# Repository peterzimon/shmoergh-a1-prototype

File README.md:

# Shmøergh A1 — Semi-modular analog monosynth

A1 is a fully analog semi-modular monosynth. I took the Minimoog as my main inspiration for its sound but of course the circuitry is nowhere comparable with it. The synth has a default hardwired patch inside, it has a couple of modulation sources and targets so we can consider it semi-modular. Everything is handmade by me at home. Most of the module circuits are based on very well-known schematics and a few of the circuits are original. 

### Features
- Fat AF analog sound, fun
- Two voices with 3 waveshapes (saw, triangle, pulse) and additional noise and square suboscillator sound sources
- 24dB/oct diode low pass filter with self-resonance and dedicated envelope generator
- Triangle and square waveform LFO
- Mod matrix for overriding default patch
- Follows Eurorack standards: 10Vpp signal and modulation, 0-8V envelope levels
- All modules are designed and built on separate PCBs for reusability and experimenting

### What's in this repo?
You can find all the **KiCad 5** files (schematics and PCB design) of the synth here.

---

### License and disclaimer
All circuits, schematics, printed circuit board, panel design and associated data published within this project can be used for private use only. The author, host, and all people associated with these circuits disclaim any liability for damages should anyone be killed or injured while working on these projects, or projects based on these designs, or any other project or design presented in these schematics. The author, host, and all people associated with these circuits also disclaim any liability for projects, or projects based on these designs, or any other project or design presented on these web pages and any associated web pages when used in such a way as to infringe relevant government regulations and by-laws.

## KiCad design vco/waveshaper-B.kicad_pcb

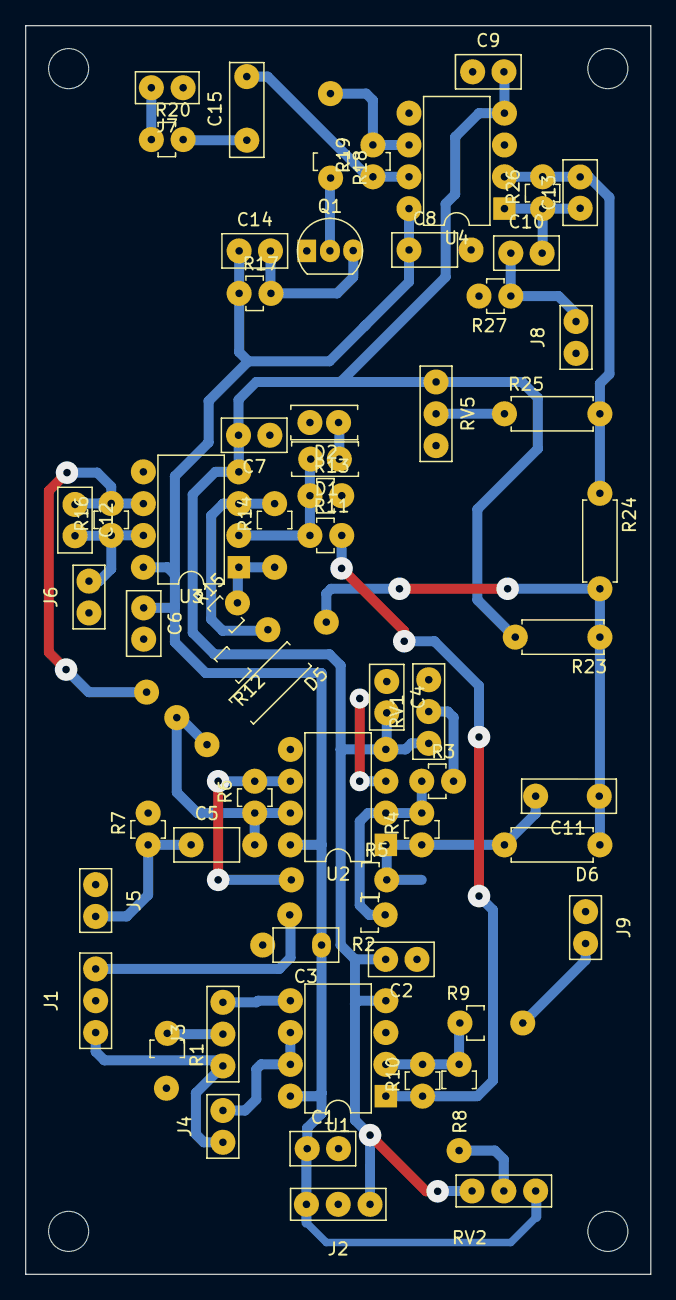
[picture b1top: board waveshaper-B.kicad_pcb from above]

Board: 2 copper layers, 49.9 x 99.7 mm, 61 parts (0 on the bottom side), 35 nets.

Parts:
C1, C2, C3, C4, C6, C7, C8, C9, C14: 100n; C_Disc_D5.0mm_W2.5mm_P2.50mm
C5, C10: 470n; C_Disc_D5.0mm_W2.5mm_P2.50mm
C11: 2.2n foil; C_Foil_P5.48mm
C12, C13: 22p; C_Disc_D5.0mm_W2.5mm_P2.50mm
C15: 1u; C_Foil_P5.48mm
D1, D2: 4.7V; D_Axial-Vertical
D5, D6: 1N4148; D_Axial
J1: In + 5VPower; NSL25_01x03_Vertical
J2: Power; NSL25_01x03_Vertical
J3: Course Switch IO; NSL25_01x03_Vertical
J4: Coarse VCO IO; NSL25_01x02_Vertical
J5: Saw Out; NSL25_01x02_Vertical
J6: Square Out; NSL25_01x02_Vertical
J7: Noise Out; NSL25_01x02_Vertical
J8: Tri Out; NSL25_01x02_Vertical
J9: PWM; NSL25_01x02_Vertical
Q1: BC548; TO-92_Inline
R1: 1.5k (0.1%); R_Axial_Vertical
R2: 10k; R_Axial_Vertical
R3, R12, R18: 2.2k; R_Axial_Vertical
R4: 15k; R_Axial_Vertical
R5, R6, R10, R16: 100k; R_Axial_Vertical
R7, R27: 1M; R_Axial_Vertical
R8: 150k; R_Axial_Vertical
R9, R11: 47k; R_Axial_Vertical
R13, R26: 220k; R_Axial_Vertical
R14: 2.2M; R_Axial_Vertical
R15: 240k; R_Axial_Vertical
R17: 470k; R_Axial_Vertical
R19: 3.3M; R_Axial_Vertical
R20: 1k; R_Axial_Vertical
R23: 10k; R_Axial_DIN0207_L6.3mm_D2.5mm_P7.62mm_Horizontal
R24, R25: 100k; R_Axial_DIN0207_L6.3mm_D2.5mm_P7.62mm_Horizontal
RV1: 10k; PinOut_01x03
RV2: 100k; NSL25_01x03_Vertical
RV5: 100k; PinOut_01x03
U1, U2, U3, U4: TL072; DIP-8_W7.62mm

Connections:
+12V: C1.1, C3.1, C6.1, C8.1, C14.1, J2.1, R17.1, RV2.1, U1.8, U2.8, U3.8, U4.8
-5V: J1.3, J3.3, J4.2
-12V: C2.2, C4.2, C7.2, C9.2, J2.3, R23.2, RV1.3, RV2.3, RV5.3, U1.4, U2.4, U3.4, U4.4
COARSE: J3.1, U1.5
CV_PWM: J9.1, R9.2
GND: C1.2, C2.1, C3.2, C4.1, C6.2, C7.1, C8.2, C9.1, D2.2, J2.2, J5.2, J6.2, J7.2, J8.2, J9.2, R1.2, R7.2, R13.2, R27.2, RV1.1, RV5.1, U1.3, U2.3, U2.5, U3.5, U4.3, U4.5
unnamed: C10.2, C13.1, R26.1, U4.1
unnamed: C11.1, D5.1, D6.1, R23.1, R24.2
unnamed: C12.1, R15.1, R16.2, U3.6
unnamed: C13.2, R24.1, R25.2, R26.2, U4.2
unnamed: C14.2, Q1.3, R17.2
unnamed: C15.1, R20.2
unnamed: C15.2, R19.1, U4.7
unnamed: D1.1, D2.1
unnamed: D1.2, R11.1, R13.1, U3.2
unnamed: J3.2, R1.1
unnamed: J4.1, U1.6, U1.7
unnamed: Q1.2, R18.2
unnamed: R2.1, R3.1, R4.2, U2.2
unnamed: R3.2, RV1.2
unnamed: R5.1, R6.2, U2.6
unnamed: R8.2, RV2.2
unnamed: R8.1, R9.1, R10.2, U1.2
unnamed: R12.1, R14.2, U3.3
unnamed: R14.1, R15.2, U3.1
unnamed: R18.1, R19.2, U4.6
unnamed: R25.1, RV5.2
OUT_NOISE: J7.1, R20.1
OUT_SAW: C5.1, J5.1, R7.1
OUT_SQR: C12.2, J6.1, R16.1, U3.7
OUT_TRI: C10.1, J8.1, R27.1
PWM: R10.1, R11.2, U1.1
RAW_SAW: J1.1, R2.2
SAW_DBL_INV: C5.2, D5.2, R6.1, R12.2, U2.7
SAW_INV: C11.2, D6.2, R4.1, R5.2, U2.1

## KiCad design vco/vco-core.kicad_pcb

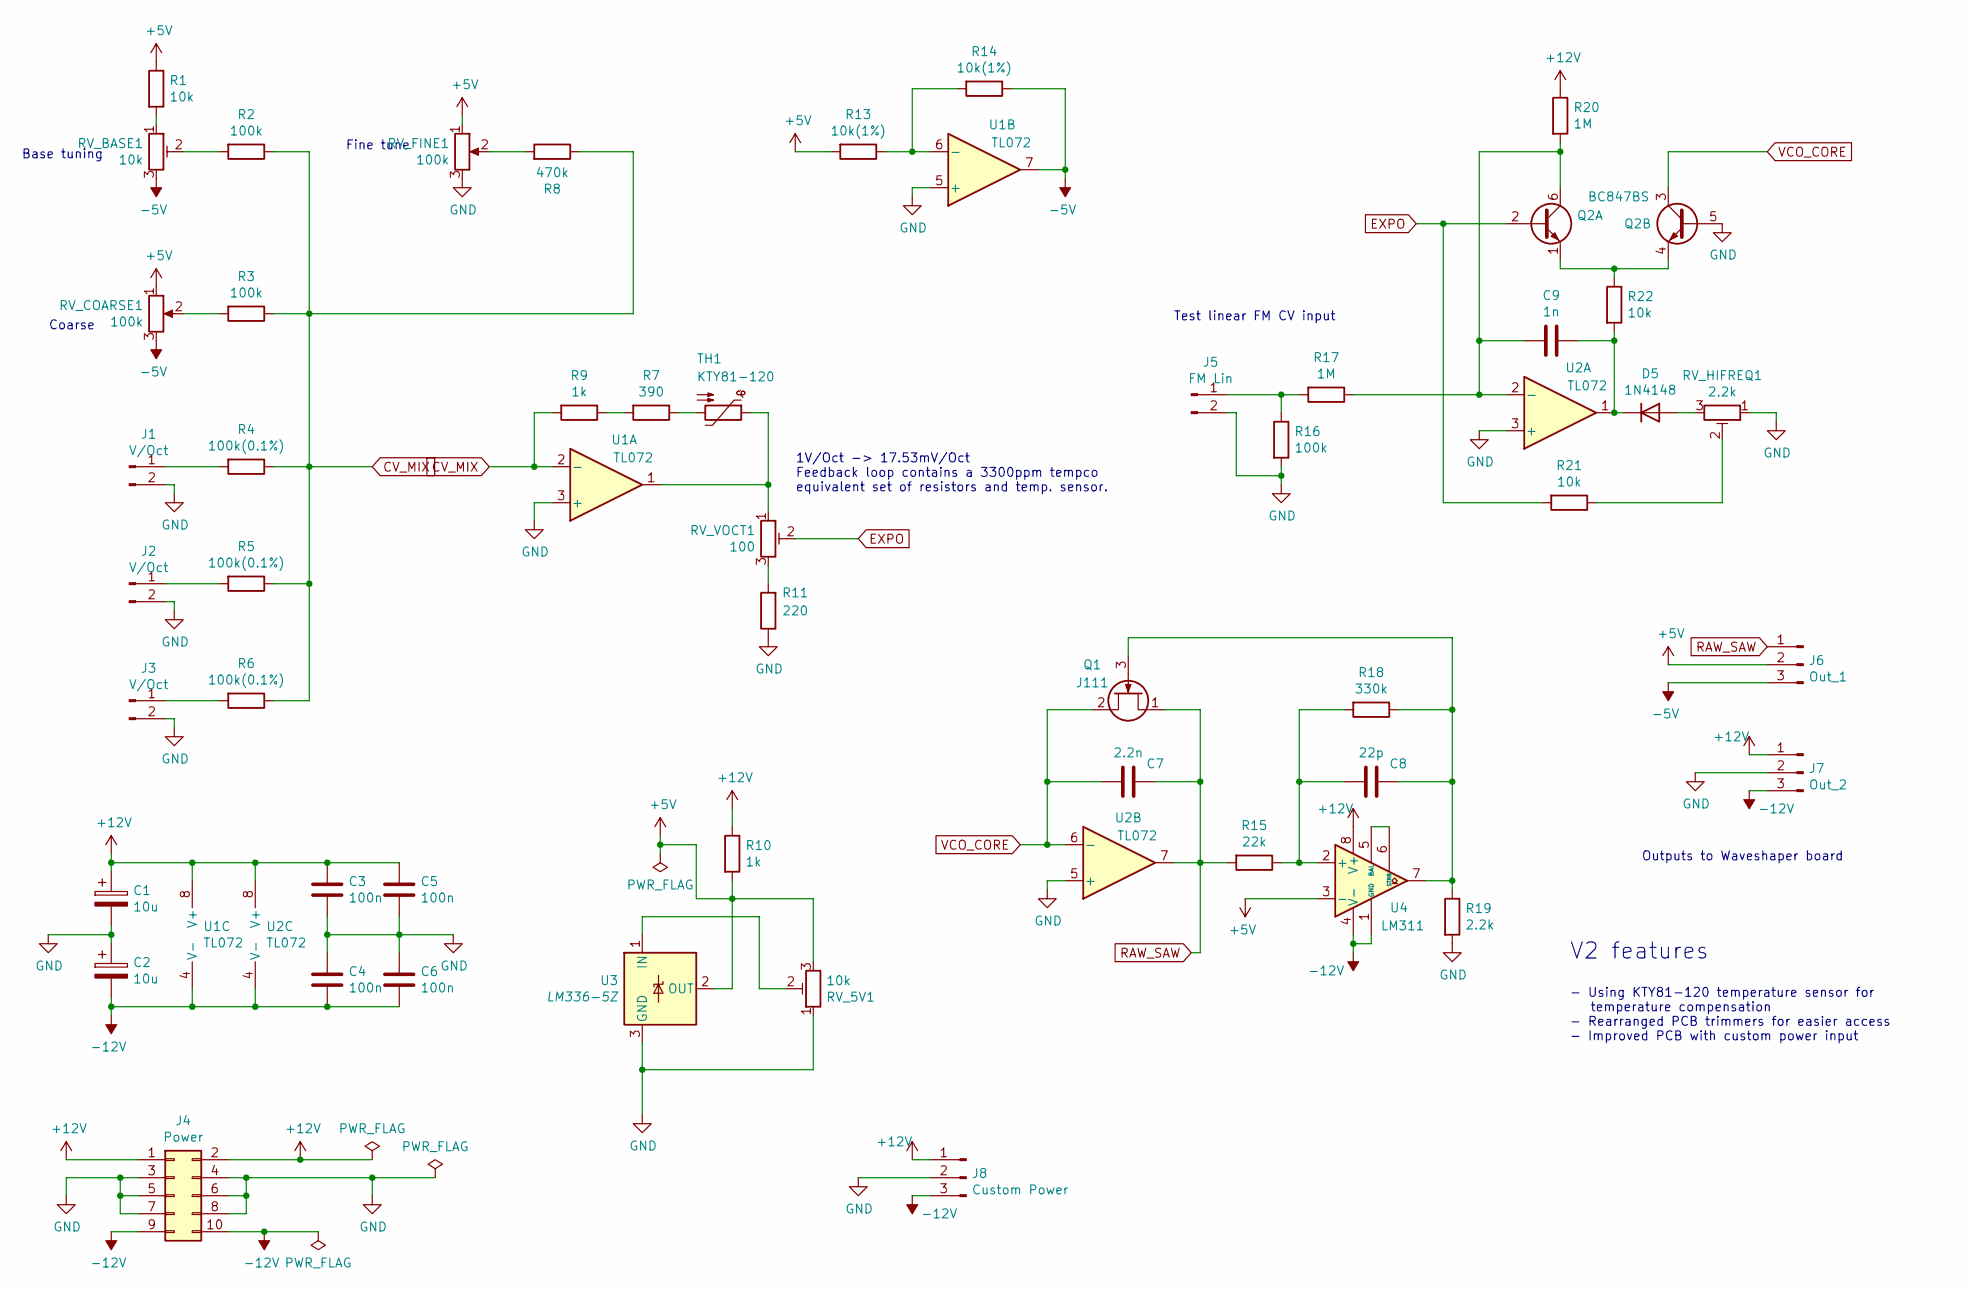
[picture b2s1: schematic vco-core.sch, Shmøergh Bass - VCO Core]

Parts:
C1, C2: 10u; CP_Radial_D5.0mm_P2.50mm
C3, C4, C5, C6: 100n; C_Disc_D5.0mm_W2.5mm_P2.50mm
C7: 2.2n; C_Disc_D5.0mm_W2.5mm_P2.50mm
C8: 22p; C_Disc_D5.0mm_W2.5mm_P2.50mm
C9: 1n; C_Disc_D5.0mm_W2.5mm_P2.50mm
D5: 1N4148; D_Axial-Vertical
J1, J2, J3: V/Oct; NSL25_01x02_Vertical
J4: Power; Eurorack_Power_Supply
J5: FM Lin; NSL25_01x02_Vertical
J6: Out_1; NSL25_01x03_Vertical
J7: Out_2; NSL25_01x03_Vertical
J8: Custom Power; NSL25_01x03_Vertical
Q1: J111; TO-92_Inline
Q2: BC847BS; SOT-363_SC-70-6
R1, R21, R22: 10k; R_Axial_Vertical
R2, R3, R16: 100k; R_Axial_Vertical
R4, R5, R6: 100k(0.1%); R_Axial_Vertical
R7: 390; R_Axial_Vertical
R8: 470k; R_Axial_Vertical
R9, R10: 1k; R_Axial_Vertical
R11: 220; R_Axial_Vertical
R13, R14: 10k(1%); R_Axial_Vertical
R15: 22k; R_Axial_Vertical
R17, R20: 1M; R_Axial_Vertical
R18: 330k; R_Axial_Vertical
R19: 2.2k; R_Axial_Vertical
RV_5V1: 10k; PinOut_01x03
RV_BASE1: 10k; PinOut_01x03
RV_COARSE1: 100k; NSL25_01x03_Vertical
RV_FINE1: 100k; NSL25_01x03_Vertical
RV_HIFREQ1: 2.2k; PinOut_01x03
RV_VOCT1: 100; PinOut_01x03
TH1: KTY81-120; R_Axial_DIN0207_L6.3mm_D2.5mm_P7.62mm_Horizontal
U1, U2: TL072; DIP-8_W7.62mm
U3: LM336-5Z; TO-92_Inline
U4: LM311; DIP-8_W7.62mm

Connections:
+5V: J6.2, R1.1, R10.2, R13.2, RV_5V1.3, RV_COARSE1.1, RV_FINE1.1, U3.2 (OUT), U4.3 (-)
+12V: C1.1, C3.1, C5.1, J4.1, J4.2, J7.1, J8.1, R10.1, R20.1, U1.8 (V+), U2.8 (V+), U4.8 (V+)
-5V: J6.3, R14.1, RV_BASE1.3, RV_COARSE1.3, U1.7
-12V: C2.2, C4.2, C6.2, J4.9, J4.10, J7.3, J8.3, U1.4 (V-), U2.4 (V-), U4.1 (GND), U4.4 (V-)
CV_MIX: R2.1, R3.1, R4.1, R5.1, R6.1, R8.1, R9.2, U1.2 (-)
EXPO: Q2.2 (B1), R21.2, RV_VOCT1.2
GND: C1.2, C2.1, C3.2, C4.1, C5.2, C6.1, J1.2, J2.2, J3.2, J4.3, J4.4, J4.5, J4.6, J4.7, J4.8, J5.2, J7.2, J8.2, Q2.5 (B2), R11.1, R16.2, R19.2, RV_5V1.1, RV_FINE1.3, RV_HIFREQ1.1, U1.3 (+), U1.5 (+), U2.3 (+), U2.5 (+), U3.3 (GND)
unnamed: C8.1, Q1.3 (G), R18.1, R19.1, U4.7
unnamed: C8.2, R15.1, R18.2, U4.2 (+)
unnamed: C9.1, D5.1 (K), R22.2, U2.1
unnamed: C9.2, Q2.6 (C1), R17.1, R20.2, U2.2 (-)
unnamed: D5.2 (A), RV_HIFREQ1.3
unnamed: J1.1, R4.2
unnamed: J2.1, R5.2
unnamed: J3.1, R6.2
unnamed: J5.1, R16.1, R17.2
unnamed: Q2.1 (E1), Q2.4 (E2), R22.1
unnamed: R1.2, RV_BASE1.1
unnamed: R2.2, RV_BASE1.2
unnamed: R3.2, RV_COARSE1.2
unnamed: R7.1, TH1.2
unnamed: R7.2, R9.1
unnamed: R8.2, RV_FINE1.2
unnamed: R11.2, RV_VOCT1.3
unnamed: R13.1, R14.2, U1.6 (-)
unnamed: R21.1, RV_HIFREQ1.2
unnamed: RV_5V1.2, U3.1 (IN)
unnamed: RV_VOCT1.1, TH1.1, U1.1
unnamed: U4.5 (BAL), U4.6 (STRB)
RAW_SAW: C7.1, J6.1, Q1.1 (D), R15.2, U2.7
VCO_CORE: C7.2, Q1.2 (S), Q2.3 (C2), U2.6 (-)

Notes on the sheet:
Coarse
Base tuning
Fine tune
Outputs to Waveshaper board
Test linear FM CV input
V2 features
- Using KTY81-120 temperature sensor for temperature compensation - Rearranged PCB trimmers for easier access - Improved PCB with custom power input
1V/Oct -> 17.53mV/Oct Feedback loop contains a 3300ppm tempco equivalent set of resistors and temp. sensor.

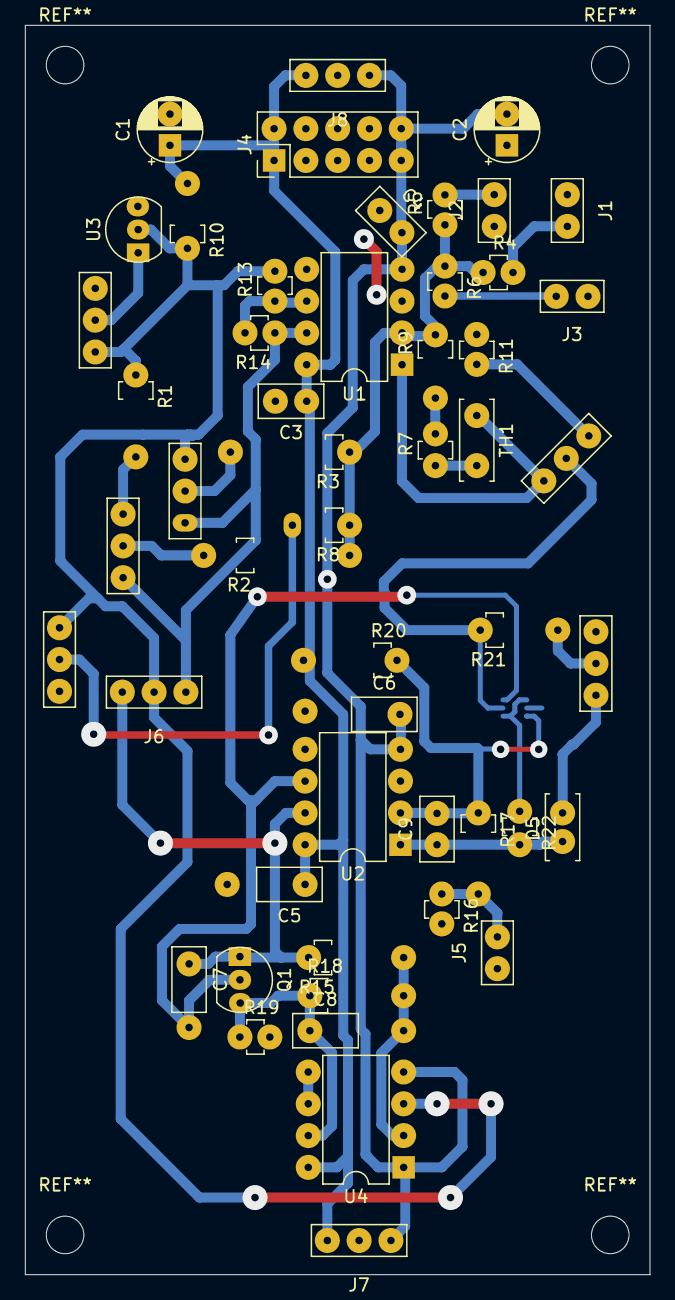
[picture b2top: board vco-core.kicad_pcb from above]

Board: 2 copper layers, 49.9 x 99.8 mm, 52 parts (1 on the bottom side), 31 nets.

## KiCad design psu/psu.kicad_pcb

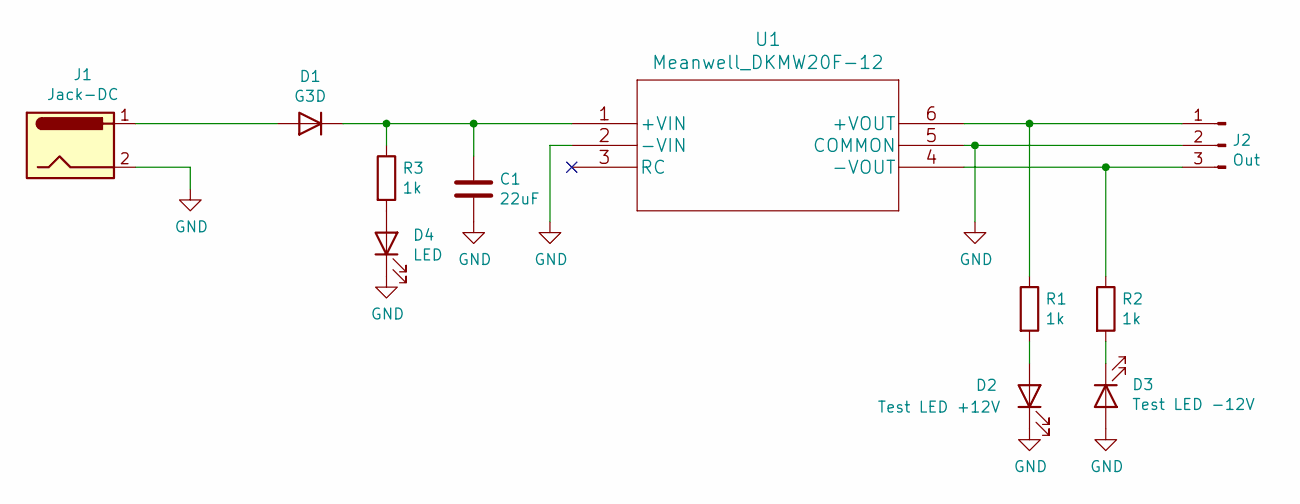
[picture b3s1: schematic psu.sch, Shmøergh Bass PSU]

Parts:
C1: 22uF; CP_Radial_D5.0mm_P2.50mm
D1: G3D; D_Axial
D2: Test LED +12V; NSL25_01x02_Vertical
D3: Test LED -12V; NSL25_01x02_Vertical
D4: LED; NSL25_01x02_Vertical
J1: Jack-DC; NSL25_01x02_Vertical
J2: Out; NSL25_01x03_Vertical
R1, R2, R3: 1k; R_Axial_DIN0207_L6.3mm_D2.5mm_P7.62mm_Horizontal
U1: Meanwell_DKMW20F-12; Meanwell_DKMWx0F_TopView

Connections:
GND: C1.2, D2.1 (K), D3.2 (A), D4.1 (K), J1.2, J2.2, U1.2 (-VIN), U1.5 (COMMON)
unnamed: C1.1, D1.1 (K), R3.1, U1.1 (+VIN)
unnamed: D1.2 (A), J1.1
unnamed: D2.2 (A), R1.2
unnamed: D3.1 (K), R2.2
unnamed: D4.2 (A), R3.2
unnamed: J2.1, R1.1, U1.6 (+VOUT)
unnamed: J2.3, R2.1, U1.4 (-VOUT)

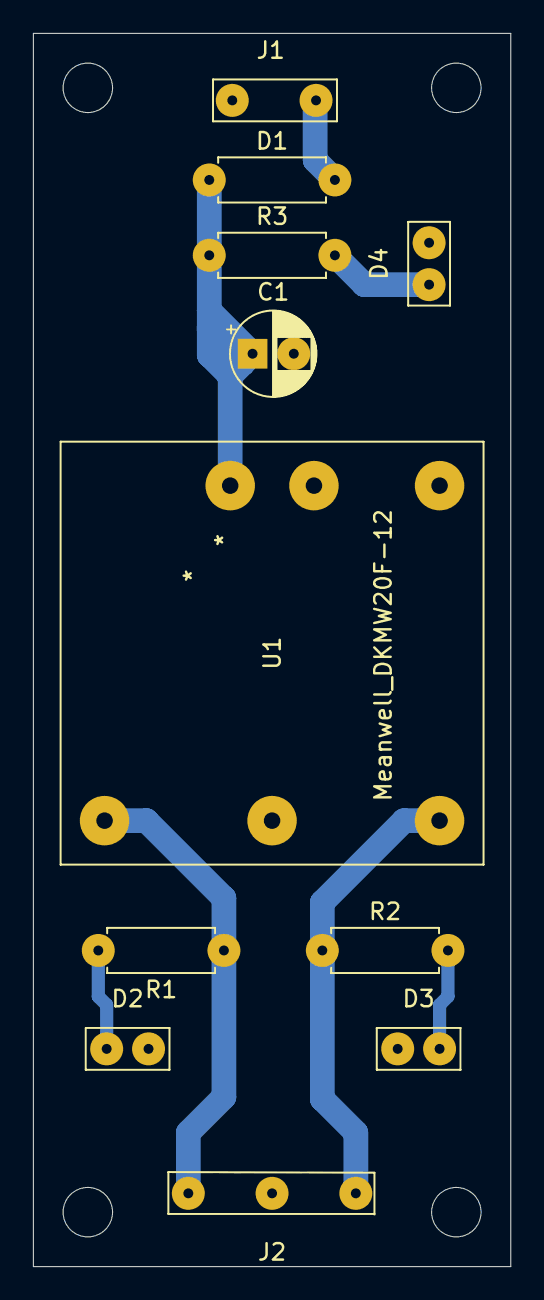
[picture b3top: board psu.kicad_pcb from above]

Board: 2 copper layers, 29.0 x 74.8 mm, 11 parts (0 on the bottom side), 8 nets.

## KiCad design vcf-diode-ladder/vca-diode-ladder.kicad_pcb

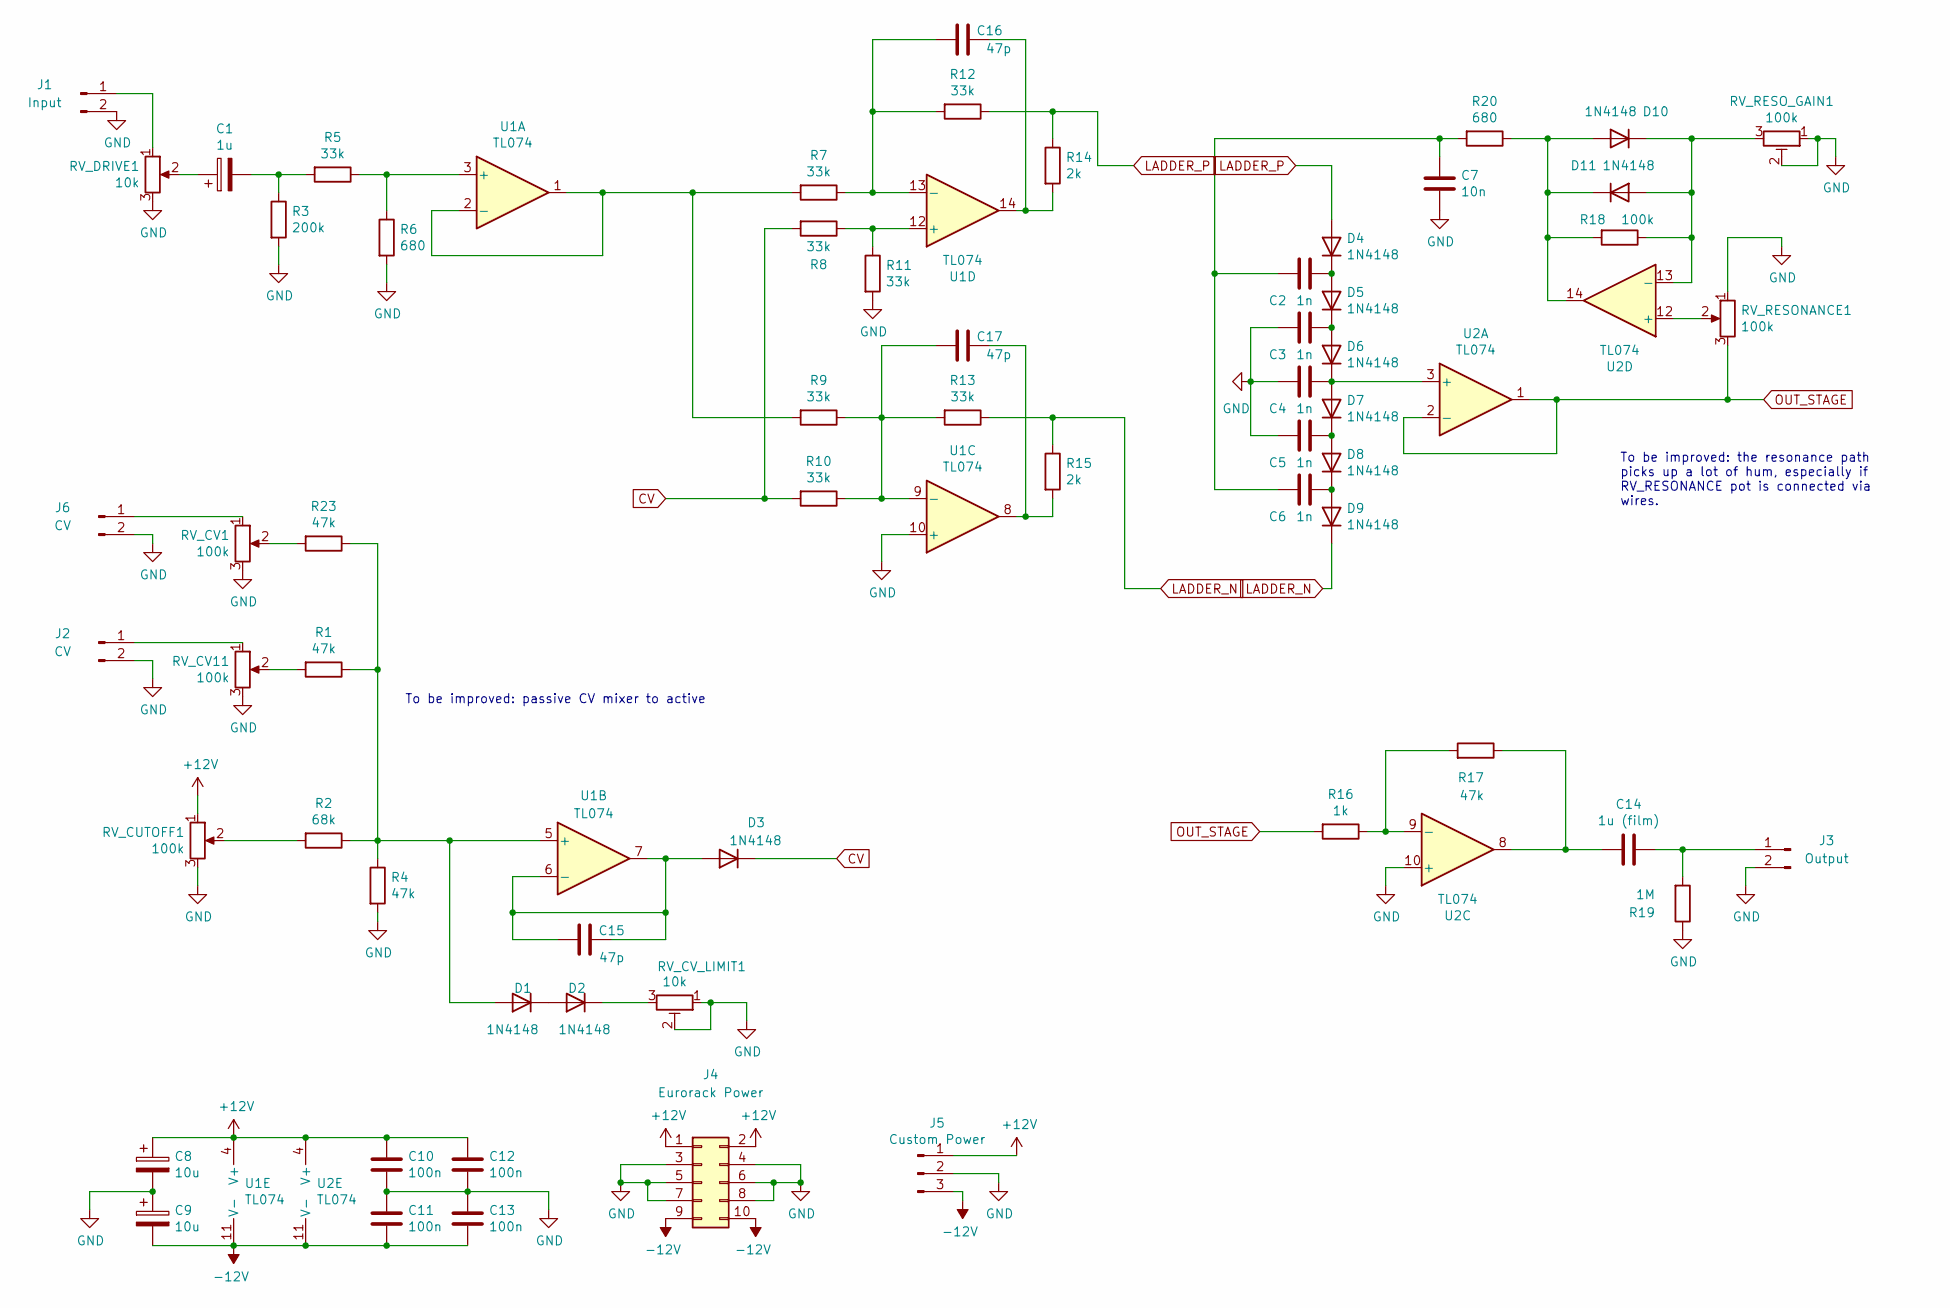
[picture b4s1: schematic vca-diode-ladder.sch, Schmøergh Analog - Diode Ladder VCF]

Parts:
C1: 1u; C_Foil_P5.48mm
C2, C3, C4, C5, C6: 1n; C_Foil_P5.48mm
C7: 10n; C_Foil_P5.48mm
C8, C9: 10u; CP_Radial_D5.0mm_P2.50mm
C10, C11, C12, C13: 100n; C_Disc_D5.0mm_W2.5mm_P2.50mm
C14: 1u (film); C_Foil_P5.48mm
C15, C16, C17: 47p; C_Disc_D5.0mm_W2.5mm_P2.50mm
D1, D2, D3, D4, D5, D6, D7, D8, D9, D10, D11: 1N4148; D_Axial-Vertical
J1: Input; JT_A25_01x02_Vertical
J2, J6: CV; JT_A25_01x02_Vertical
J3: Output; JT_A25_01x02_Vertical
J4: Eurorack Power; Eurorack_Power_Supply
J5: Custom Power; NSL25_01x03_Vertical
R1, R4, R17, R23: 47k; R_Axial_Vertical
R2: 68k; R_Axial_Vertical
R3: 200k; R_Axial_Vertical
R5, R7, R8, R9, R10, R11, R12, R13: 33k; R_Axial_Vertical
R6, R20: 680; R_Axial_Vertical
R14, R15: 2k; R_Axial_Vertical
R16: 1k; R_Axial_Vertical
R18: 100k; R_Axial_Vertical
R19: 1M; R_Axial_Vertical
RV_CUTOFF1: 100k; JT_A25_01x03_Vertical
RV_CV1, RV_CV11: 100k; JT_A25_01x03_Vertical
RV_CV_LIMIT1: 10k; TrimPot_Vertical
RV_DRIVE1: 10k; JT_A25_01x03_Vertical
RV_RESONANCE1: 100k; JT_A25_01x03_Vertical
RV_RESO_GAIN1: 100k; TrimPot_Vertical
U1, U2: TL074; DIP-14_W7.62mm

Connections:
+12V: C8.1, C10.1, C12.1, J4.1, J4.2, J5.1, RV_CUTOFF1.1, U1.4 (V+), U2.4 (V+)
-12V: C9.2, C11.2, C13.2, J4.9, J4.10, J5.3, U1.11 (V-), U2.11 (V-)
CV: D3.1 (K), R8.2, R10.2
GND: C3.2, C4.2, C5.2, C7.2, C8.2, C9.1, C10.2, C11.1, C12.2, C13.1, J1.2, J2.2, J3.2, J4.3, J4.4, J4.5, J4.6, J4.7, J4.8, J5.2, J6.2, R3.2, R4.2, R6.2, R11.2, R19.1, RV_CUTOFF1.3, RV_CV1.3, RV_CV11.3, RV_CV_LIMIT1.1, RV_CV_LIMIT1.2, RV_DRIVE1.3, RV_RESONANCE1.1, RV_RESO_GAIN1.1, RV_RESO_GAIN1.2, U1.10 (+), U2.10 (+)
LADDER_N: D9.1 (K), R13.1, R15.1
LADDER_P: D4.2 (A), R12.1, R14.1
unnamed: C1.1, RV_DRIVE1.2
unnamed: C1.2, R3.1, R5.2
unnamed: C2.1, D4.1 (K), D5.2 (A)
unnamed: C2.2, C6.2, C7.1, R20.2
unnamed: C3.1, D5.1 (K), D6.2 (A)
unnamed: C4.1, D6.1 (K), D7.2 (A), U2.3 (+)
unnamed: C5.1, D7.1 (K), D8.2 (A)
unnamed: C6.1, D8.1 (K), D9.2 (A)
unnamed: C14.1, J3.1, R19.2
unnamed: C14.2, R17.1, U2.8
unnamed: C15.1, C15.2, D3.2 (A), U1.6 (-), U1.7
unnamed: C16.1, R14.2, U1.14
unnamed: C16.2, R7.1, R12.2, U1.13 (-)
unnamed: C17.1, R15.2, U1.8
unnamed: C17.2, R9.1, R10.1, R13.2, U1.9 (-)
unnamed: D1.1 (K), D2.2 (A)
unnamed: D1.2 (A), R1.1, R2.1, R4.1, R23.1, U1.5 (+)
unnamed: D2.1 (K), RV_CV_LIMIT1.3
unnamed: D10.1 (K), D11.2 (A), R18.1, RV_RESO_GAIN1.3, U2.13 (-)
unnamed: D10.2 (A), D11.1 (K), R18.2, R20.1, U2.14
unnamed: J1.1, RV_DRIVE1.1
unnamed: J2.1, RV_CV11.1
unnamed: J6.1, RV_CV1.1
unnamed: R1.2, RV_CV11.2
unnamed: R2.2, RV_CUTOFF1.2
unnamed: R5.1, R6.1, U1.3 (+)
unnamed: R7.2, R9.2, U1.1, U1.2 (-)
unnamed: R8.1, R11.1, U1.12 (+)
unnamed: R16.1, R17.2, U2.9 (-)
unnamed: R23.2, RV_CV1.2
unnamed: RV_RESONANCE1.2, U2.12 (+)
OUT_STAGE: R16.2, RV_RESONANCE1.3, U2.1, U2.2 (-)

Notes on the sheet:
To be improved: passive CV mixer to active
To be improved: the resonance path picks up a lot of hum, especially if RV_RESONANCE pot is connected via wires.

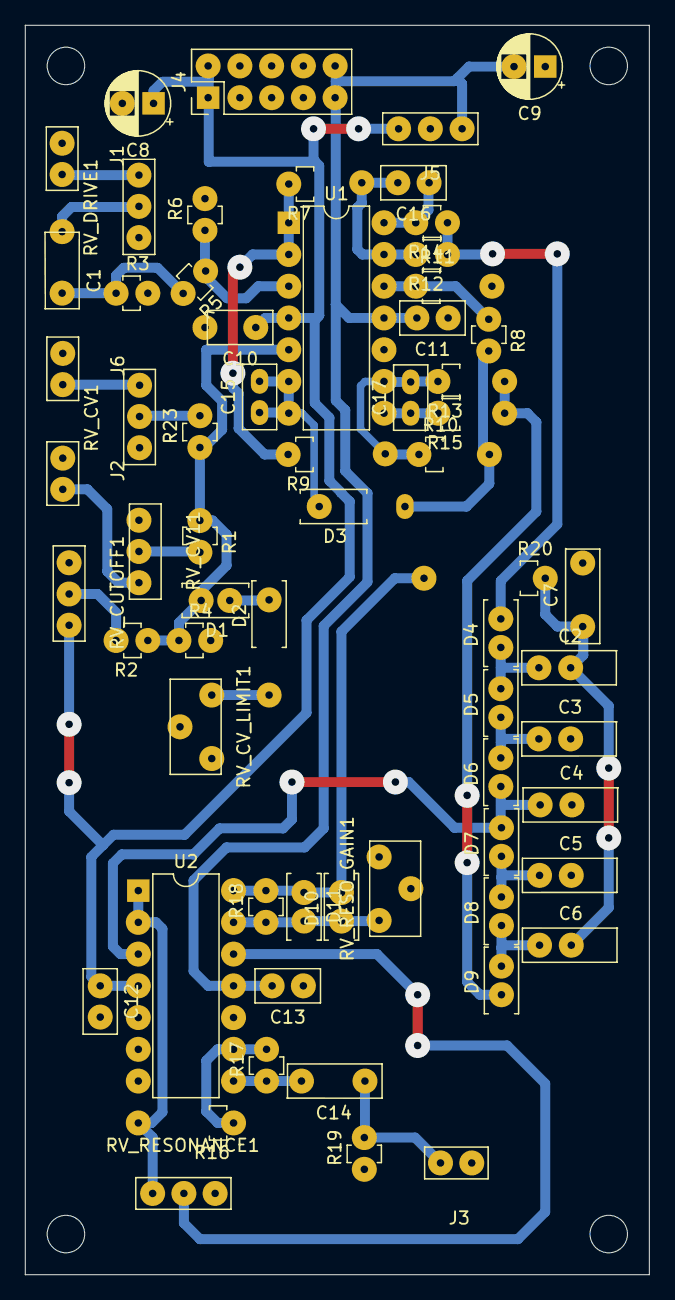
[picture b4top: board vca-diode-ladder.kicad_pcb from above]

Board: 2 copper layers, 49.9 x 100.0 mm, 64 parts (0 on the bottom side), 38 nets.

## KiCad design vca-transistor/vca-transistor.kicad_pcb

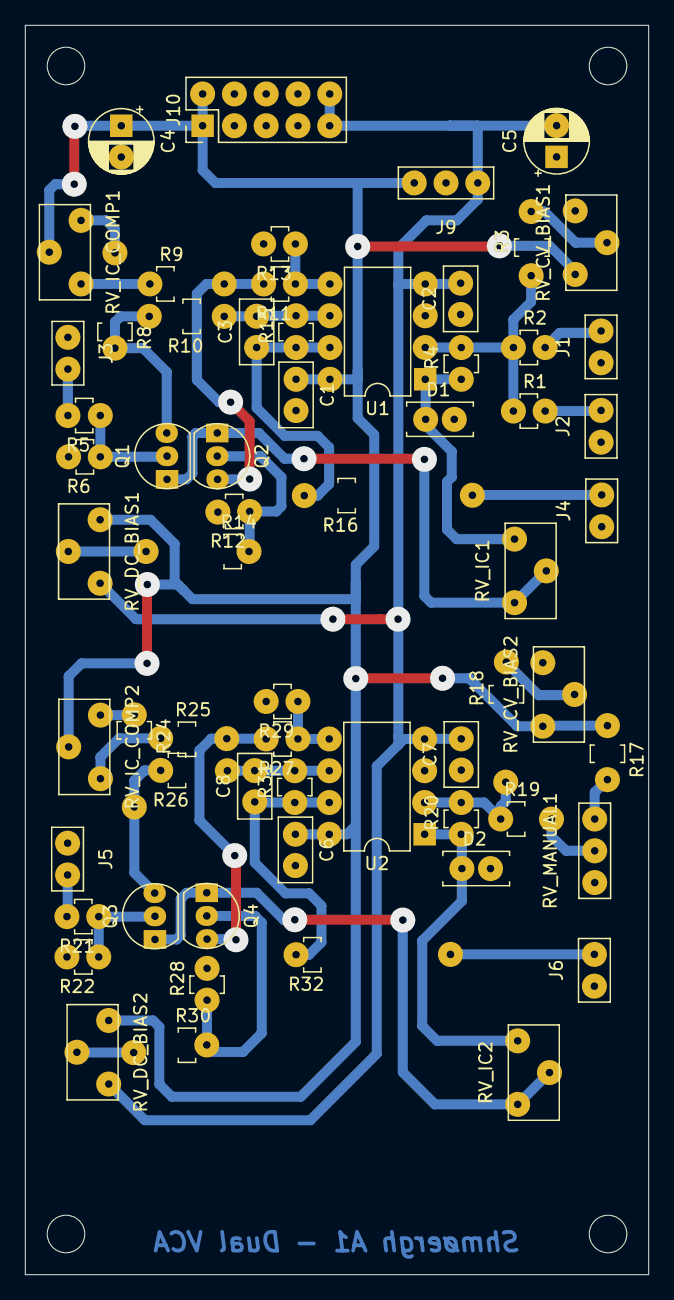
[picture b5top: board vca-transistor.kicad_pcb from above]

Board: 2 copper layers, 49.8 x 99.9 mm, 63 parts (0 on the bottom side), 39 nets.

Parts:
C1, C2, C6, C7: 100n; C_Disc_D5.0mm_W2.5mm_P2.50mm
C3, C8: 47p; C_Disc_D5.0mm_W2.5mm_P2.50mm
C4, C5: 10u; CP_Radial_D5.0mm_P2.50mm
D1, D2: 1N4148; D_Axial-Vertical
J1: MOD_CV_IN; NSL25_01x02_Vertical
J2: CV_IN; NSL25_01x02_Vertical
J3: SIGNAL_IN; NSL25_01x02_Vertical
J4: AUDIO_OUT; NSL25_01x02_Vertical
J5: LFO IN; NSL25_01x02_Vertical
J6: LFO_OUT; NSL25_01x02_Vertical
J9: Custom Power; NSL25_01x03_Vertical
J10: Eurorack Power; Eurorack_Power_Supply
Q1, Q2, Q3, Q4: 2N3904; TO-92_Inline
R1: 470k; R_Axial_Vertical
R2: 150k; R_Axial_Vertical
R3, R18: 240k; R_Axial_Vertical
R4, R20: 33k; R_Axial_Vertical
R5, R8, R9, R21, R24, R25: 100k; R_Axial_Vertical
R6, R12, R22, R28: 220; R_Axial_Vertical
R10, R11, R26, R27: 10k; R_Axial_Vertical
R13, R15, R29, R31: 680k; R_Axial_Vertical
R14, R30: 1M; R_Axial_Vertical
R16, R32: 1k; R_Axial_Vertical
R17: 4.7k; R_Axial_Vertical
R19: 200k; R_Axial_Vertical
RV_CV_BIAS1, RV_CV_BIAS2: 100k; TrimPot_Vertical
RV_DC_BIAS1, RV_DC_BIAS2: 100k; TrimPot_Vertical
RV_IC1, RV_IC2: 10k; TrimPot_Vertical
RV_IC_COMP1, RV_IC_COMP2: 2.2k; TrimPot_Vertical
RV_MANUAL1: 10k; NSL25_01x03_Vertical
U1, U2: TL072; DIP-8_W7.62mm

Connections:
+12V: C1.1, C4.1, C6.1, J9.1, J10.1, J10.2, R17.1, RV_CV_BIAS1.3, RV_CV_BIAS2.3, RV_DC_BIAS1.3, RV_DC_BIAS2.3, RV_IC_COMP1.2, RV_IC_COMP2.2, U1.8, U2.8
-12V: C2.2, C5.2, C7.2, J9.3, J10.9, J10.10, RV_DC_BIAS1.1, RV_DC_BIAS2.1, U1.4, U2.4
GND: C1.2, C2.1, C4.2, C5.1, C6.2, C7.1, D1.2, D2.2, J1.2, J2.2, J3.2, J4.2, J5.2, J6.2, J9.2, J10.3, J10.4, J10.5, J10.6, J10.7, J10.8, R6.2, R12.2, R13.2, R22.2, R28.2, R29.2, RV_CV_BIAS1.1, RV_CV_BIAS2.1, RV_MANUAL1.3, U1.3, U2.3
unnamed: C3.1, R15.1, R16.2, U1.7
unnamed: C3.2, R10.1, R15.2, U1.6
unnamed: C8.1, R31.1, R32.2, U2.7
unnamed: C8.2, R26.1, R31.2, U2.6
unnamed: D1.1, R4.1, RV_IC1.1, U1.1
unnamed: D2.1, R20.1, RV_IC2.1, U2.1
unnamed: J1.1, R2.2
unnamed: J2.1, R1.2
unnamed: J3.1, R5.2
unnamed: J4.1, R16.1
unnamed: J5.1, R21.2
unnamed: J6.1, R32.1
unnamed: Q1.1, Q2.1, RV_IC1.2, RV_IC1.3
unnamed: Q1.2, R5.1, R6.1
unnamed: Q1.3, R8.2, R10.2
unnamed: Q2.2, R12.1, R14.2
unnamed: Q2.3, R9.2, R11.2
unnamed: Q3.1, Q4.1, RV_IC2.2, RV_IC2.3
unnamed: Q3.2, R21.1, R22.1
unnamed: Q3.3, R24.2, R26.2
unnamed: Q4.2, R28.1, R30.2
unnamed: Q4.3, R25.2, R27.2
unnamed: R1.1, R2.1, R3.1, R4.2, U1.2
unnamed: R3.2, RV_CV_BIAS1.2
unnamed: R8.1, RV_IC_COMP1.3
unnamed: R9.1, RV_IC_COMP1.1
unnamed: R11.1, R13.1, U1.5
unnamed: R14.1, RV_DC_BIAS1.2
unnamed: R17.2, RV_MANUAL1.1
unnamed: R18.1, R19.1, R20.2, U2.2
unnamed: R18.2, RV_CV_BIAS2.2
unnamed: R19.2, RV_MANUAL1.2
unnamed: R24.1, RV_IC_COMP2.3
unnamed: R25.1, RV_IC_COMP2.1
unnamed: R27.1, R29.1, U2.5
unnamed: R30.1, RV_DC_BIAS2.2

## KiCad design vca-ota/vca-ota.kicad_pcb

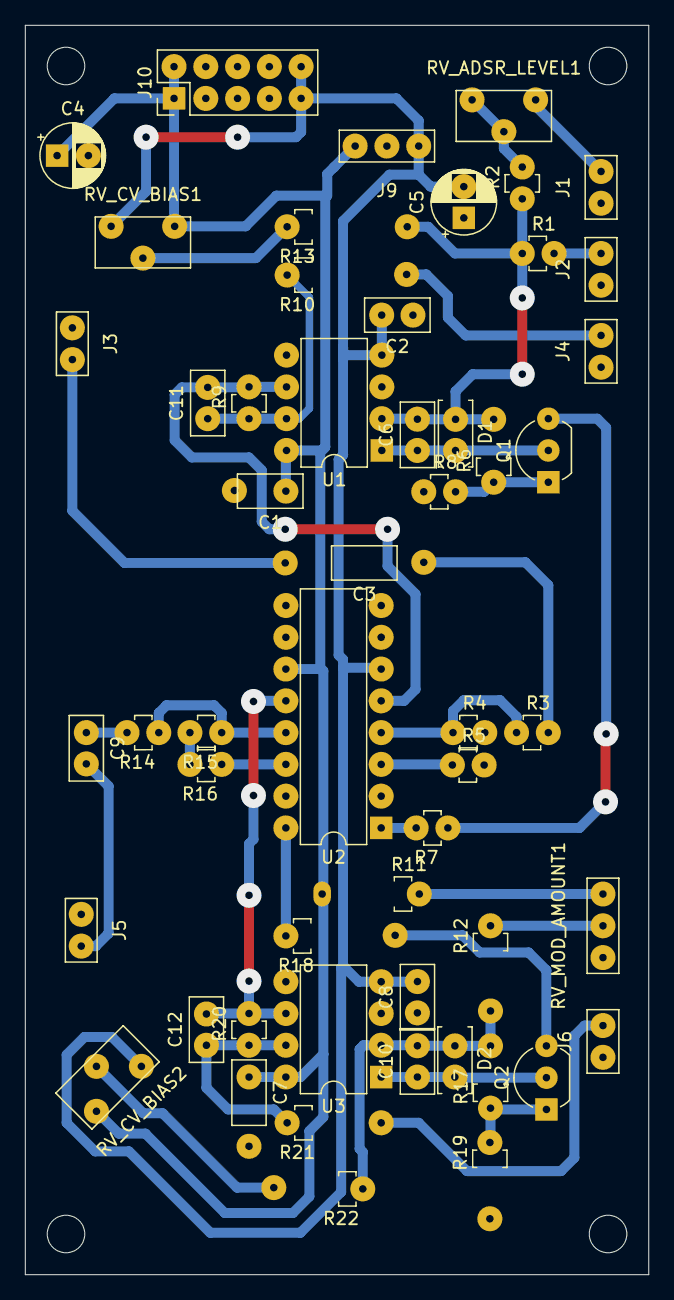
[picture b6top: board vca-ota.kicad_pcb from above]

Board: 2 copper layers, 49.8 x 99.9 mm, 53 parts (0 on the bottom side), 34 nets.

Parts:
C1, C2, C7, C8: 100n; C_Disc_D5.0mm_W2.5mm_P2.50mm
C3, C9: 470n; C_Disc_D5.0mm_W2.5mm_P2.50mm
C4, C5: 10u; CP_Radial_D5.0mm_P2.50mm
C6, C10: 1n; C_Disc_D5.0mm_W2.5mm_P2.50mm
C11, C12: 47p; C_Disc_D5.0mm_W2.5mm_P2.50mm
D1, D2: 1N4148; D_Axial-Vertical
J1: ADSR_CV; NSL25_01x02_Vertical
J2: MOD_MATRIX_CV; NSL25_01x02_Vertical
J3, J5: INPUT; NSL25_01x02_Vertical
J4, J6: OUTPUT; NSL25_01x02_Vertical
J9: Custom Power; NSL25_01x03_Vertical
J10: Eurorack Power; Eurorack_Power_Supply
Q1, Q2: 2N3906; TO-92_Inline_Wide
R1, R12: 240k; R_Axial_Vertical
R2: 330k; R_Axial_Vertical
R3, R14: 100k; R_Axial_Vertical
R4, R5, R15, R16: 620; R_Axial_Vertical
R6, R9, R17, R20: 33k; R_Axial_Vertical
R7, R18: 6.8k; R_Axial_Vertical
R8, R10, R19, R21: 1k; R_Axial_Vertical
R11: 15k; R_Axial_Vertical
R13, R22: 680k; R_Axial_Vertical
RV_ADSR_LEVEL1: 100k; TrimPot_Vertical
RV_CV_BIAS1, RV_CV_BIAS2: 10k; TrimPot_Vertical
RV_MOD_AMOUNT1: 10k; NSL25_01x03_Vertical
U1, U3: TL072; DIP-8_W7.62mm
U2: LM13700; DIP-16_W7.62mm

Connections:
+12V: C1.1, C4.1, C7.1, J9.1, J10.1, J10.2, R11.1, RV_CV_BIAS1.1, RV_CV_BIAS2.1, U1.8, U2.11, U3.8
-12V: C2.2, C5.2, C8.2, J9.3, J10.9, J10.10, RV_CV_BIAS1.3, RV_CV_BIAS2.3, U1.4, U2.6, U3.4
GND: C1.2, C2.1, C4.2, C5.1, C7.2, C8.1, J1.2, J2.2, J3.2, J4.2, J5.2, J6.2, J9.2, J10.3, J10.4, J10.5, J10.6, J10.7, J10.8, R4.2, R5.2, R8.1, R15.2, R16.2, R19.1, RV_MOD_AMOUNT1.3, U1.3, U1.5, U2.7, U2.10, U3.3, U3.5
unnamed: C3.1, R3.2
unnamed: C3.2, J3.1
unnamed: C6.1, D1.2, Q1.2, U1.1
unnamed: C6.2, D1.1, R1.1, R2.1, R6.2, R13.1, U1.2
unnamed: C9.1, R14.2
unnamed: C9.2, J5.1
unnamed: C10.1, D2.2, Q2.2, U3.1
unnamed: C10.2, D2.1, R12.1, R17.2, R22.1, U3.2
unnamed: C11.1, R9.1, R10.2, U1.7
unnamed: C11.2, R9.2, U1.6, U2.5
unnamed: C12.1, R20.1, R21.2, U3.7
unnamed: C12.2, R20.2, U2.12, U3.6
unnamed: J1.1, RV_ADSR_LEVEL1.1
unnamed: J2.1, R1.2
unnamed: J4.1, R10.1
unnamed: J6.1, R21.1
unnamed: Q1.1, R6.1, R8.2
unnamed: Q1.3, R7.1
unnamed: Q2.1, R17.1, R19.2
unnamed: Q2.3, R18.1
unnamed: R2.2, RV_ADSR_LEVEL1.2, RV_ADSR_LEVEL1.3
unnamed: R3.1, R4.1, U2.4
unnamed: R5.1, U2.3
unnamed: R7.2, U2.1
unnamed: R11.2, RV_MOD_AMOUNT1.1
unnamed: R12.2, RV_MOD_AMOUNT1.2
unnamed: R13.2, RV_CV_BIAS1.2
unnamed: R14.1, R15.1, U2.13
unnamed: R16.1, U2.14
unnamed: R18.2, U2.16
unnamed: R22.2, RV_CV_BIAS2.2

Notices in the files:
parts and their libraries:
Copyright 2021 Accelerated Designs. All rights reserved.
